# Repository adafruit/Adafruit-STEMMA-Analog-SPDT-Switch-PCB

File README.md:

## Adafruit STEMMA Analog SPDT Switch - MAX4544 12V - JST PH 2mm PCB

<a href="http://www.adafruit.com/products/5892"><br/>
Click here to purchase one from the Adafruit shop</a>

PCB files for the Adafruit STEMMA Analog SPDT Switch - MAX4544 12V - JST PH 2mm. 

Format is EagleCAD schematic and board layout
* https://www.adafruit.com/product/5892

### Description

Analog switches are a solid state alternative to relays, when you want a smaller, lower-power technology that won't wear out mechanically. As the name implies, you can use an analog switch chip to select between two analog signals, much like a mechanical switch. These chips tend to be tiny surface mount parts, so the Adafruit STEMMA Analog SPDT Switch lets anyone use the MAX4544 SPDT analog switch for signals up to 12V, without fiddly soldering.

When the selection signal is low, the Common pin is connected to the Normally Closed (NC) pin and disconnected from the Normally Open (NO) pin. When the selection signal is high, the Common pin is connected to NO and disconnected from NC. 

Unlike a relay or mechanical switch, analog switches don't wear out, and the switch time is near instant, about 30nS. The MAX4544 chip also guarantees break-before-make so the NC and NO pins will never accidentally cross-connect. 

However, there's a few things to watch out for:

* The V+ power pin (also the red wire if using a STEMMA cable) must as high as the highest analog voltages you want to switch. That means if the analog signals are no more than 6VDC, the V+ pin must be higher than 6V. You cannot power this pin with 3.3V and switch 12V signals.
* The MAX4544 cannot switch signals below ground. No negative voltages can be applied to the COM/NO/NC pins!
* Analog switches are for signals, not power! Since this is not a mechanical switch, the signals pass through circuitry that is not designed to source or sink current. This is great for analog signal voltages, and is not good for providing more than a few mA of current.

This board has a simple plug-and-play JST PH (2mm pitch) input connector for solderless use. Provide V+ power (from 3V up to 12V) and signal of at least 2.5VDC logic level. On the output is a terminal block with the common, Normally Open and Normally Closed signals. You can also get to all the signal and power pins on a 0.1" breakout header if desired.

### License

Adafruit invests time and resources providing this open source design, please support Adafruit and open-source hardware by purchasing products from [Adafruit](https://www.adafruit.com)!

Designed by Limor Fried/Ladyada for Adafruit Industries.

Creative Commons Attribution/Share-Alike, all text above must be included in any redistribution. 
See license.txt for additional details.

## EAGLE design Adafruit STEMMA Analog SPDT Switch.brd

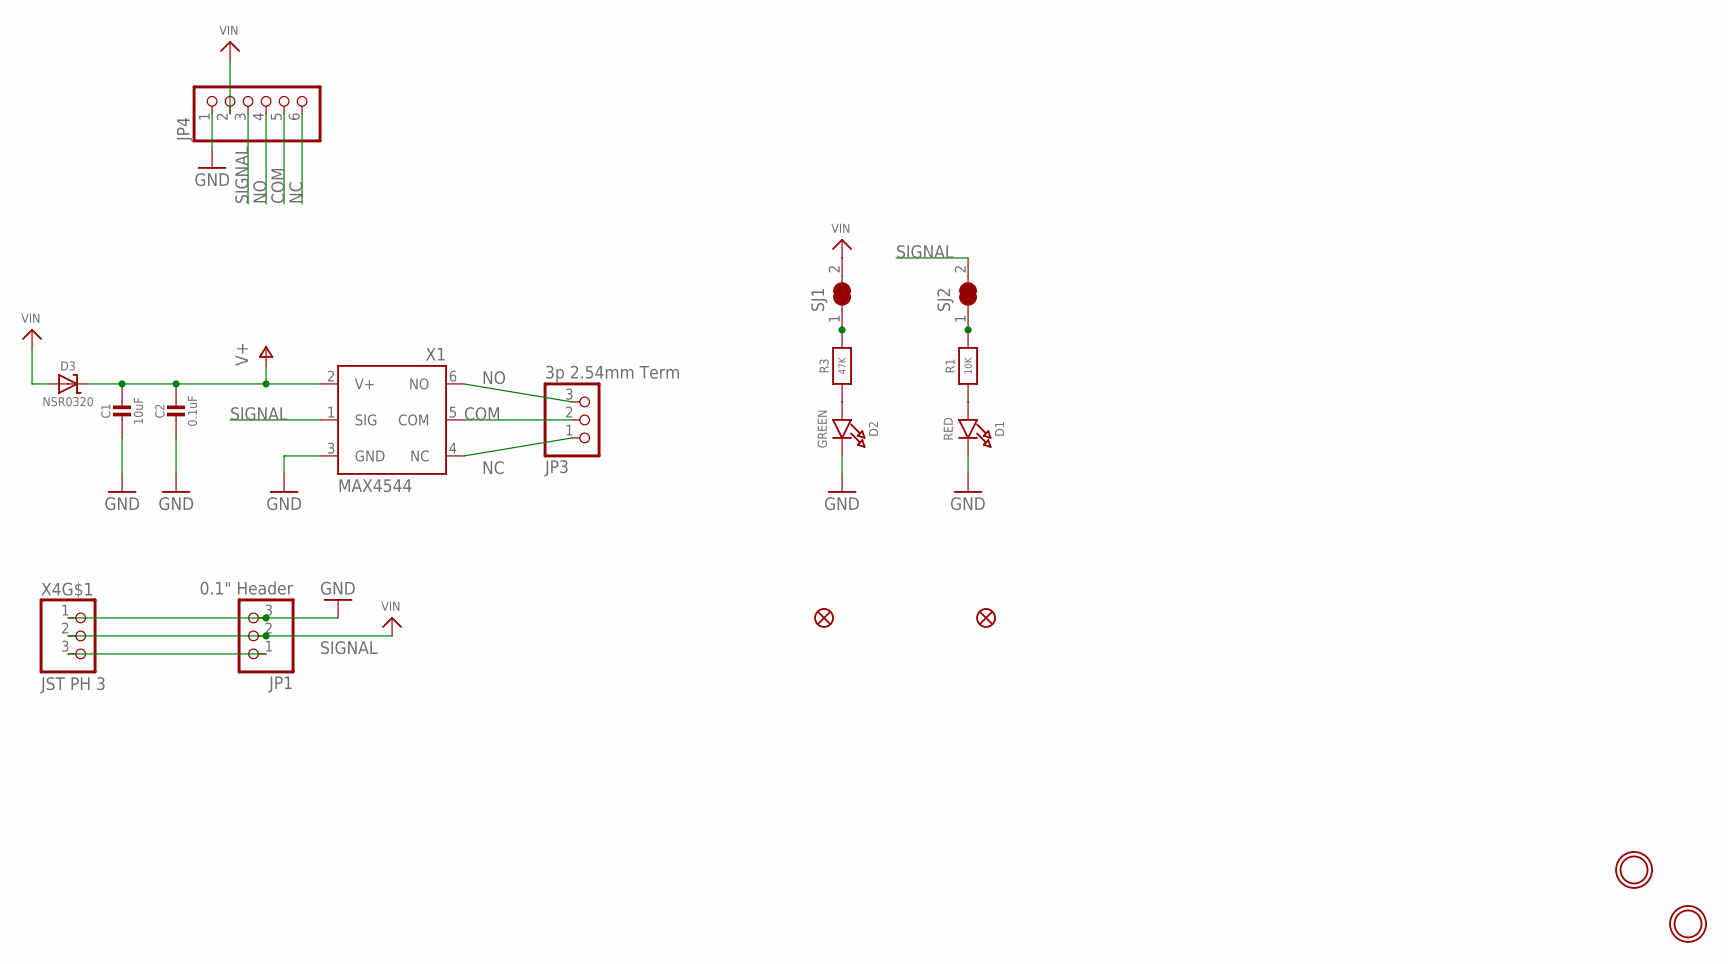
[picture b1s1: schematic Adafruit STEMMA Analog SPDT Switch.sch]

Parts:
C1: 10uF; 0805-NO
C2: 0.1uF; 0603-NO
D1: RED; CHIPLED_0603_NOOUTLINE
D2: GREEN; CHIPLED_0603_NOOUTLINE
D3: NSR0320; SOD-323
FID2, FID3: FIDUCIAL_1MM
JP1: 0.1" Header; 1X03_OVAL
JP3: 3p 2.54mm Term; 1X03_2.54MMTERMINAL
JP4: HEADER-1X676MIL_FULLROUND; 1X06_ROUND_FULL_76
R1: 10K; 0603-NO
R3: 47K; 0603-NO
SJ1, SJ2: SOLDERJUMPER_CLOSED; SOLDERJUMPER_CLOSEDWIRE
U$1, U$8: MOUNTINGHOLE2.5; MOUNTINGHOLE_2.5_PLATED
X1: MAX4544; SOT23-6
X4: JST PH 3; JSTPH3

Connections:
COM: JP3.2, JP4.5, X1.5 (COM)
GND: C1.2, C2.2, D1.C, D2.C, JP1.3, JP4.1, X1.3 (GND), X4.1
unnamed: R3.2, SJ1.1
unnamed: D1.A, R1.1
unnamed: R1.2, SJ2.1
unnamed: D2.A, R3.1
NC: JP3.1, JP4.6, X1.4 (NC)
NO: JP3.3, JP4.4, X1.6 (NO)
SIGNAL: JP1.1, JP4.3, SJ2.2, X1.1 (SIG), X4.3
V+: C1.1, C2.1, D3.C, X1.2 (V+)
VIN: D3.A, JP1.2, JP4.2, SJ1.2, X4.2

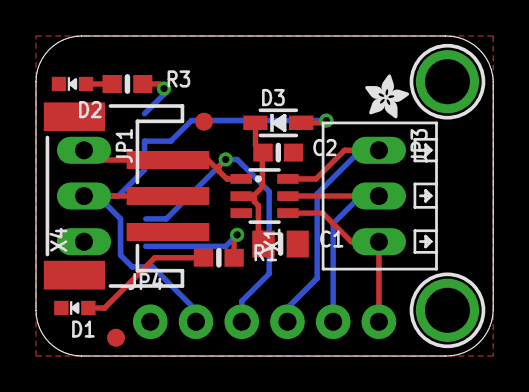
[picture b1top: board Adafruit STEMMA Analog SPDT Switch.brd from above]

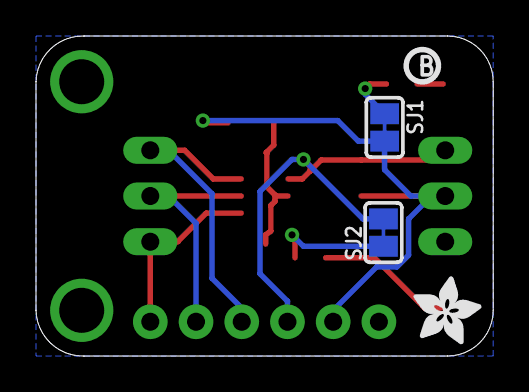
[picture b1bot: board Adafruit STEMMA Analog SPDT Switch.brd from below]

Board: 2 copper layers, 25.4 x 17.8 mm, 38 parts (9 on the bottom side), 11 nets.

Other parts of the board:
PLABEL0: PLABEL0
PLABEL1: PLABEL1
PLABEL2: PLABEL2
PLABEL3: PLABEL3
PLABEL4: PLABEL4
PLABEL5: PLABEL5
PLABEL6: PLABEL6
PLABEL7: PLABEL7
PLABEL8: PLABEL8
PLABEL9: PLABEL9
PLABEL10: PLABEL10
PLABEL11: PLABEL11
PLABEL12: PLABEL12
PLABEL13: PLABEL13
PLABEL14: PLABEL14
PLABEL15: PLABEL15
PLABEL16: PLABEL16
U$3: PCBFEAT-REV-040
U$12: ADAFRUIT_3.5MM
U$19: ADAFRUIT_2.5MM

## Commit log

2024-03-04 adding cookiecutter
2024-03-04 changing image
2024-03-04 rename

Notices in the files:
parts and their libraries:
microbuilder: This work is placed in the public domain, and may be freely used for commercial and non-commercial work with the following conditions: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
